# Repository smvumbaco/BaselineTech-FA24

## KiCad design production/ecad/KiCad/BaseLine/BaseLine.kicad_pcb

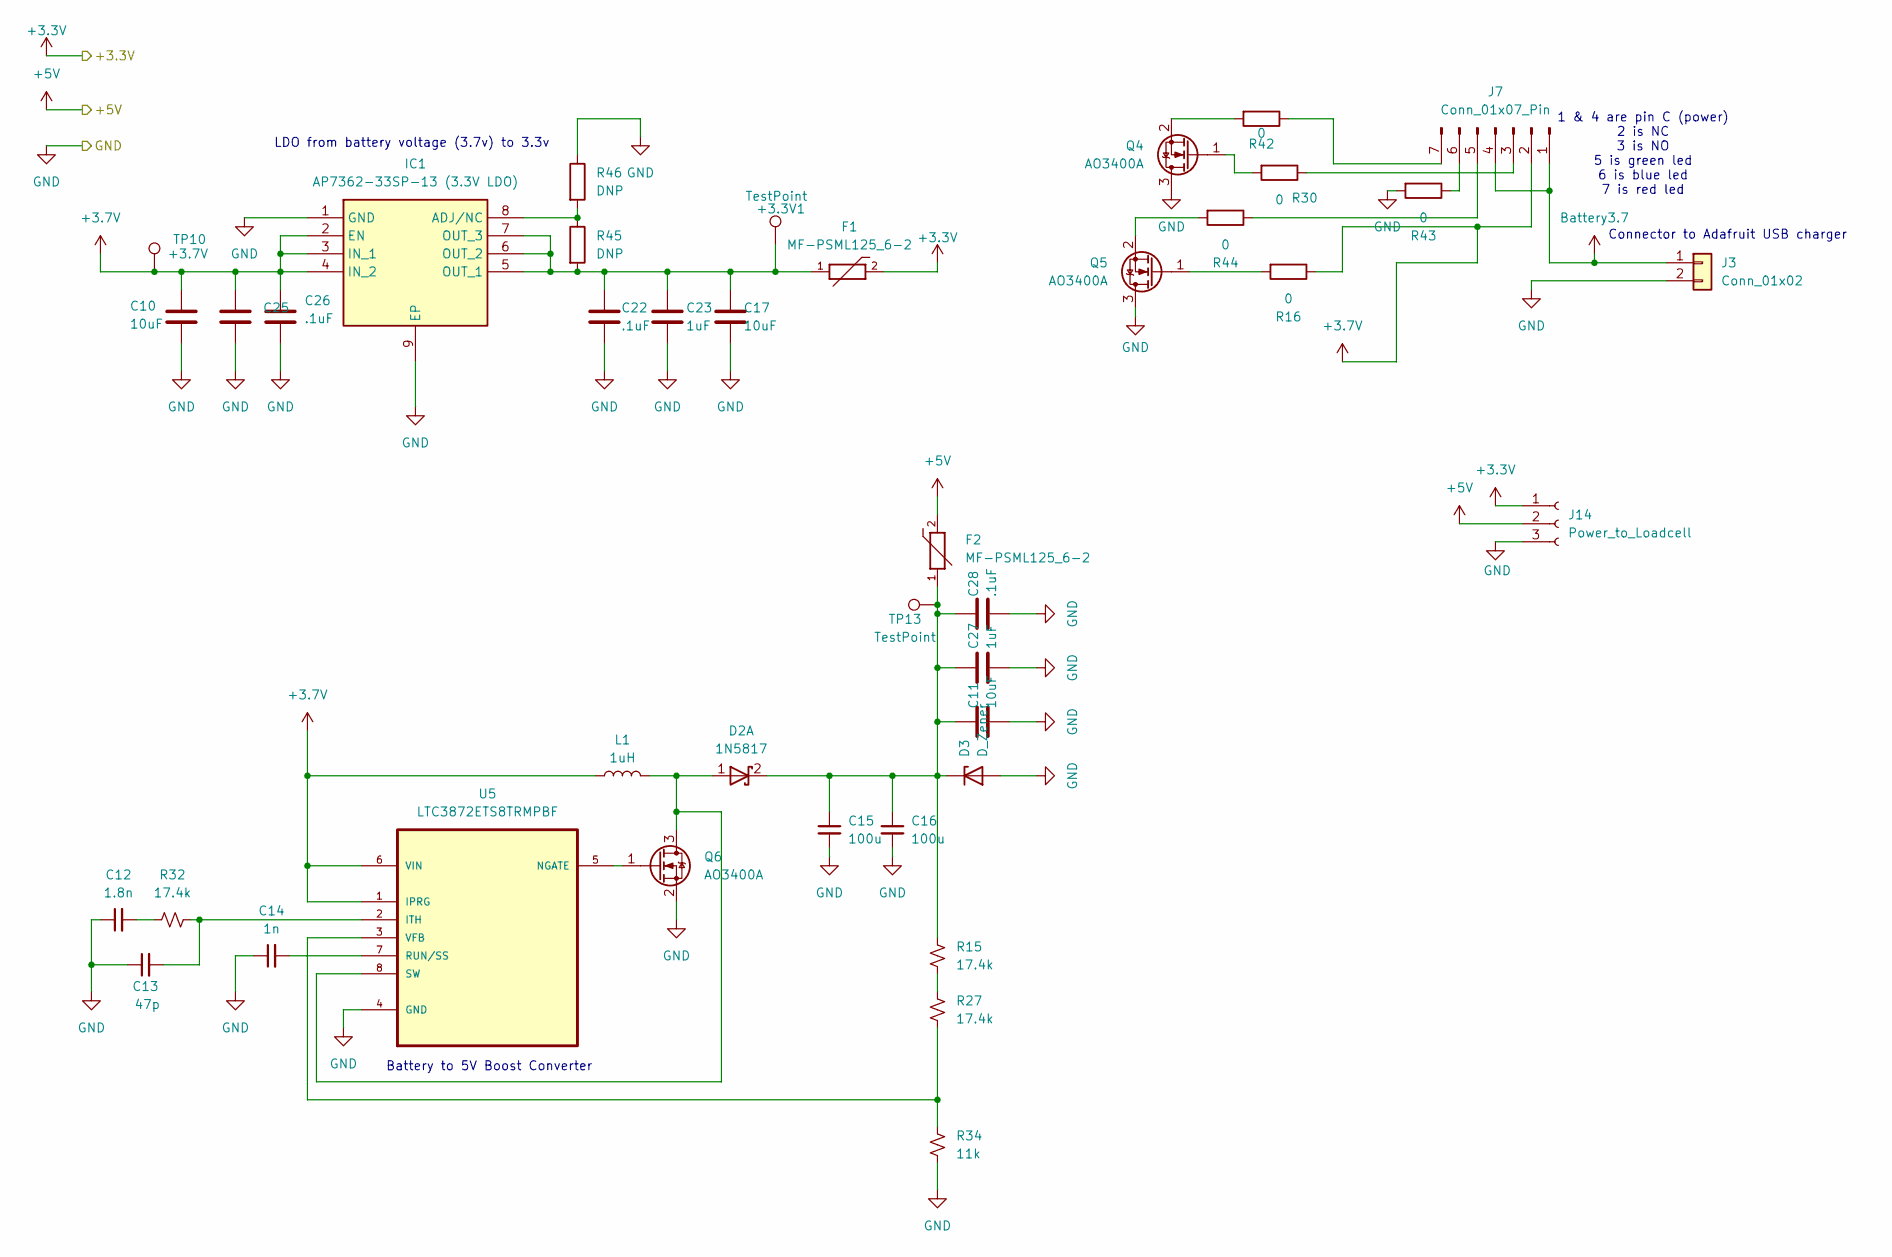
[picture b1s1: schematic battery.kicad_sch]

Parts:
+3.3V1: TestPoint; TestPoint_Pad_D1.5mm
C10, C11, C17: 10uF; C_0805_2012Metric
C12: 1.8n; C_0805_2012Metric
C13: 47p; C_0805_2012Metric
C14: 1n; C_0805_2012Metric
C15, C16: 100u; C_0805_2012Metric
C22, C26, C28: .1uF; C_0805_2012Metric
C23, C25, C27: 1uF; C_0805_2012Metric
D2: 1N5817; DO-41_STM
D3: D_Zener; DIOAD1165W56L425D185
F1, F2: MF-PSML125_6-2; FUSE_MF-PSML125_6-2; PARTREV C
IC1: AP7362-33SP-13 (3.3V LDO); SOIC127P600X163-9N; Mouser Part Number 621-AP7362-33SP-13
J3: Conn_01x02; JST_PH_B2B-PH-K_1x02_P2.00mm_Vertical
J7: Conn_01x07_Pin; JST_PH_B7B-PH-K_1x07_P2.00mm_Vertical
J14: Power_to_Loadcell; JST_EH_B3B-EH-A_1x03_P2.50mm_Vertical
L1: 1uH; L_0805_2012Metric_Pad1.05x1.20mm_HandSolder
Q4, Q5, Q6: AO3400A; SOT-23
R15, R27, R32: 17.4k; R_0805_2012Metric
R16, R30, R42, R43, R44: 0; R_0805_2012Metric
R34: 11k; R_0805_2012Metric
R45, R46: DNP; R_0805_2012Metric
TP10: +3.7V; TestPoint_Pad_2.0x2.0mm
TP13: TestPoint; TestPoint_Pad_2.0x2.0mm
U5: LTC3872ETS8TRMPBF; SOT65P280X100-8N; MPN LTC3872ETS8#TRMPBF

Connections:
+3.3V: F1.2, J14.1; also elsewhere on the board
+3.7V: C10.2, C25.2, C26.2, IC1.2 (EN), IC1.3 (IN_1), IC1.4 (IN_2), J7.2, L1.1, R16.1, TP10.1, U5.1 (IPRG), U5.6 (VIN)
+5V: F2.2, J14.2; also elsewhere on the board
Battery3.7: J3.1, J7.1, J7.4
GND: C10.1, C11.1, C12.1, C13.1, C14.1, C15.2, C16.2, C17.1, C22.1, C23.1, C25.1, C26.1, C27.1, C28.1, D3.2 (A), IC1.1 (GND), IC1.9 (EP), J3.2, J14.3, Q4.3 (D), Q5.3 (D), Q6.2 (S), R34.2, R43.2, R46.1, U5.4 (GND); also elsewhere on the board
unnamed: C12.2, R32.1
unnamed: D2.1 (A), L1.2, Q6.3 (D), U5.8 (SW)
unnamed: C11.2, C15.1, C16.1, C27.2, C28.2, D2.2 (K), D3.1 (K), F2.1, R15.2, TP13.1
unnamed: IC1.8 (ADJ/NC), R45.1, R46.2
unnamed: +3.3V1.1, C17.2, C22.2, C23.2, F1.1, IC1.5 (OUT_1), IC1.6 (OUT_2), IC1.7 (OUT_3), R45.2
unnamed: J7.3, R30.1
unnamed: J7.5, R44.1
unnamed: J7.6, R43.1
unnamed: J7.7, R42.1
unnamed: Q4.1 (G), R30.2
unnamed: Q4.2 (S), R42.2
unnamed: Q5.1 (G), R16.2
unnamed: Q5.2 (S), R44.2
unnamed: Q6.1 (G), U5.5 (NGATE)
unnamed: R15.1, R27.2
unnamed: C13.2, R32.2, U5.2 (ITH)
unnamed: C14.2, U5.7 (RUN/SS)
unnamed: R27.1, R34.1, U5.3 (VFB)

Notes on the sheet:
1 & 4 are pin C (power) 2 is NC 3 is NO 5 is green led 6 is blue led 7 is red led
LDO from battery voltage (3.7v) to 3.3v
Battery to 5V Boost Converter
Connector to Adafruit USB charger

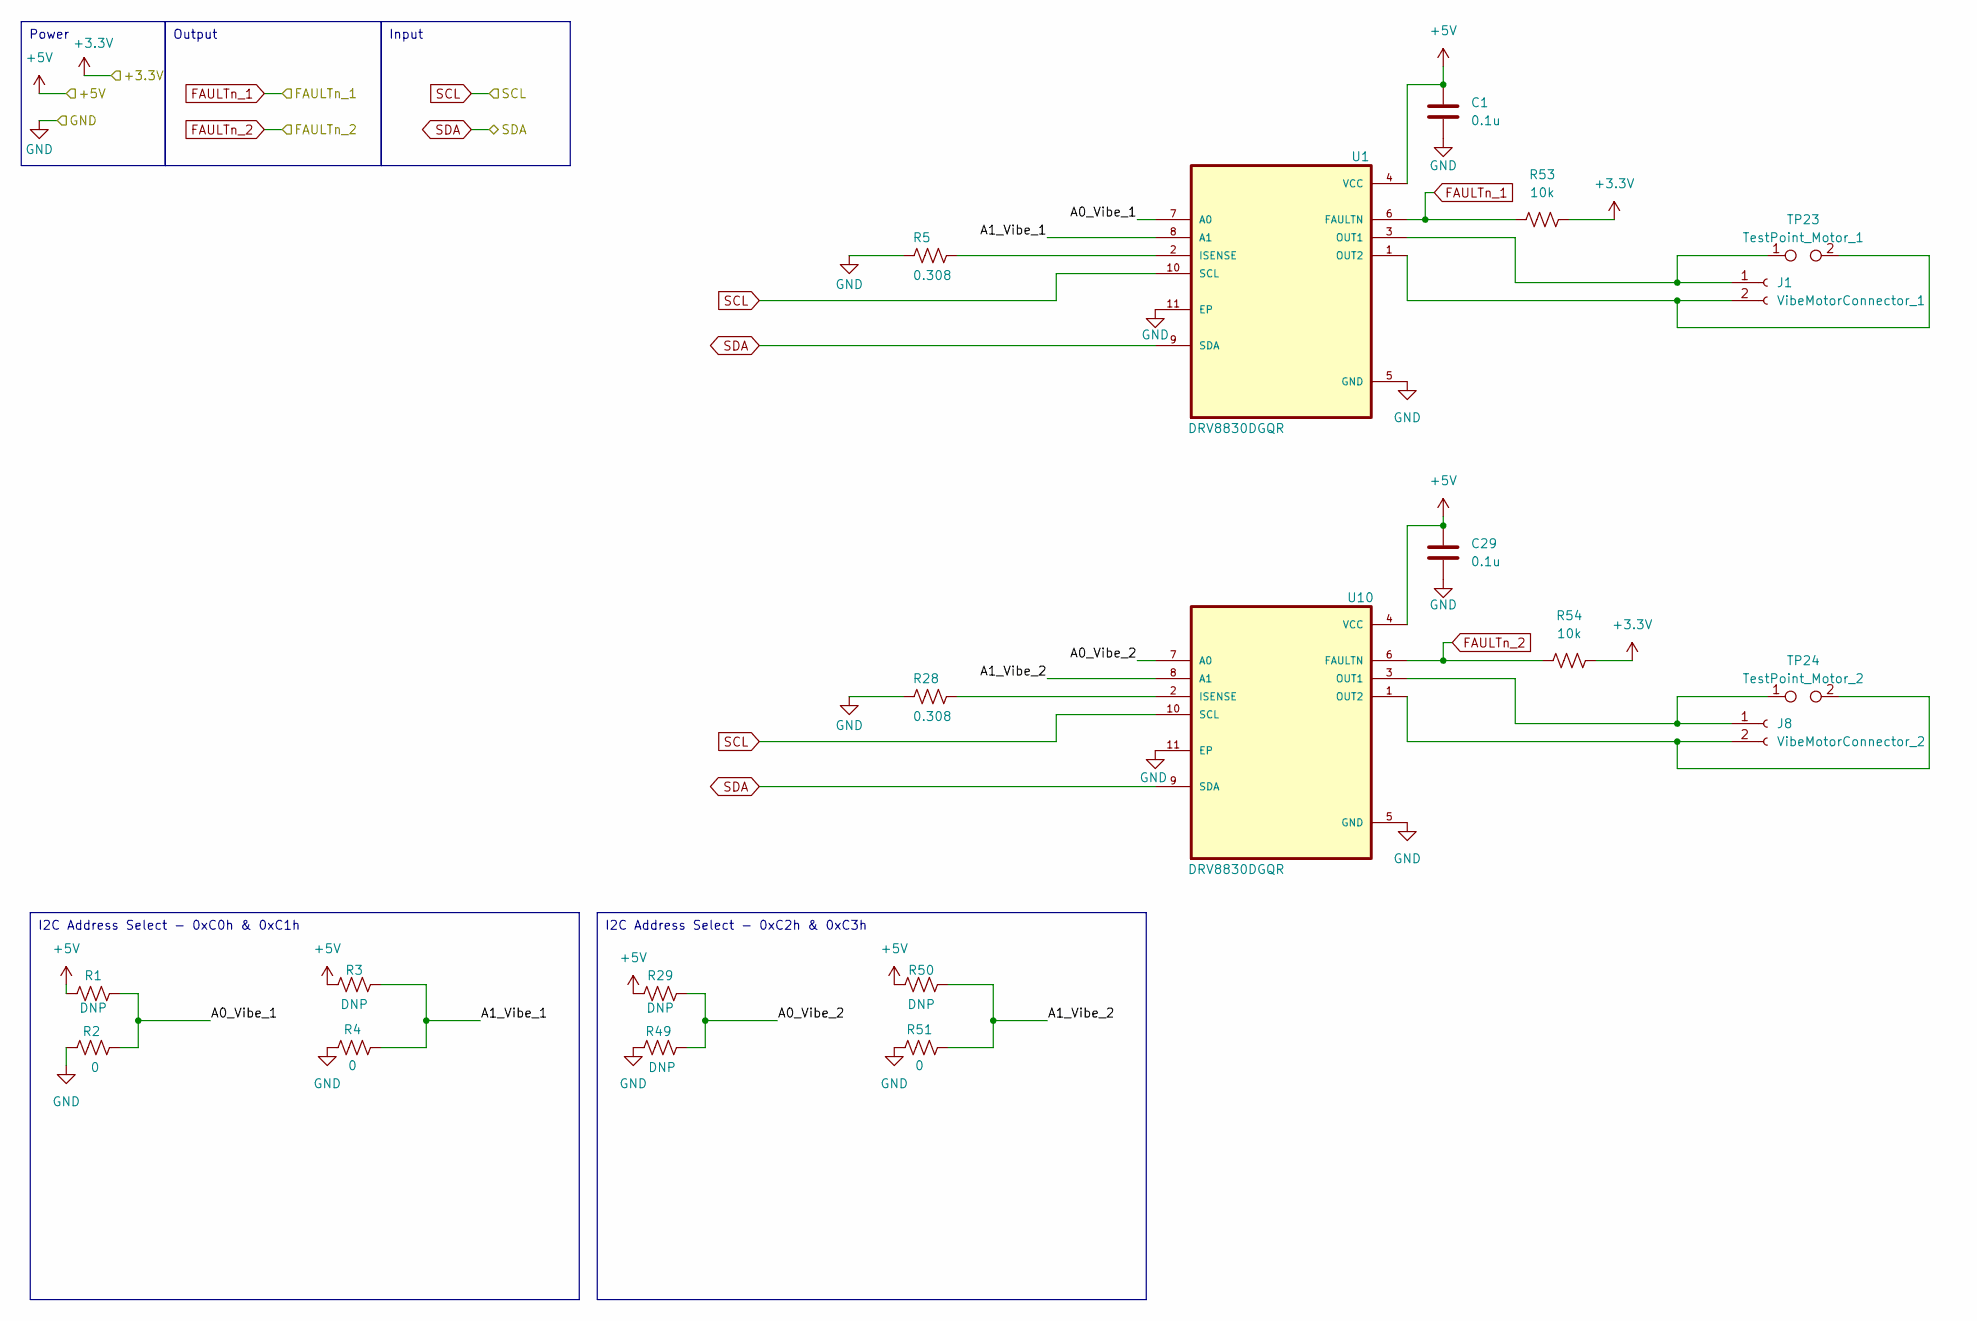
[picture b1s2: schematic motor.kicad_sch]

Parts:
C1, C29: 0.1u; C_0805_2012Metric_Pad1.18x1.45mm_HandSolder
J1: VibeMotorConnector_1; JST_B2B-XH-A
J8: VibeMotorConnector_2; JST_B2B-XH-A
R1, R3, R29, R49, R50: DNP; R_0805_2012Metric_Pad1.20x1.40mm_HandSolder
R2, R4, R51: 0; R_0805_2012Metric_Pad1.20x1.40mm_HandSolder
R5, R28: 0.308; R_0805_2012Metric_Pad1.20x1.40mm_HandSolder
R53, R54: 10k; R_0805_2012Metric_Pad1.20x1.40mm_HandSolder
TP23: TestPoint_Motor_1; TestPoint_2Pads_Pitch2.54mm_Drill0.8mm
TP24: TestPoint_Motor_2; TestPoint_2Pads_Pitch2.54mm_Drill0.8mm
U1, U10: DRV8830DGQR; IC_XTR111AIDGQR

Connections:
+3.3V: R53.2, R54.2; also elsewhere on the board
+5V: C1.1, C29.1, R1.1, R3.1, R29.1, R50.1, U1.4 (VCC), U10.4 (VCC); also elsewhere on the board
/Motor/A0_Vibe_1: R1.2, R2.2, U1.7 (A0)
/Motor/A0_Vibe_2: R29.2, R49.2, U10.7 (A0)
/Motor/A1_Vibe_1: R3.2, R4.2, U1.8 (A1)
/Motor/A1_Vibe_2: R50.2, R51.2, U10.8 (A1)
FAULTn_1: R53.1, U1.6 (FAULTN); also elsewhere on the board
FAULTn_2: R54.1, U10.6 (FAULTN); also elsewhere on the board
GND: C1.2, C29.2, R2.1, R4.1, R5.2, R28.2, R49.1, R51.1, U1.5 (GND), U1.11 (EP), U10.5 (GND), U10.11 (EP); also elsewhere on the board
unnamed: J1.1, TP23.1, U1.3 (OUT1)
unnamed: J1.2, TP23.2, U1.1 (OUT2)
unnamed: J8.1, TP24.1, U10.3 (OUT1)
unnamed: J8.2, TP24.2, U10.1 (OUT2)
unnamed: R5.1, U1.2 (ISENSE)
unnamed: R28.1, U10.2 (ISENSE)
SCL: U1.10 (SCL), U10.10 (SCL); also elsewhere on the board
SDA: U1.9 (SDA), U10.9 (SDA); also elsewhere on the board

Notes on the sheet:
Power
I2C Address Select - 0xC0h & 0xC1h
I2C Address Select - 0xC2h & 0xC3h
Output
Input

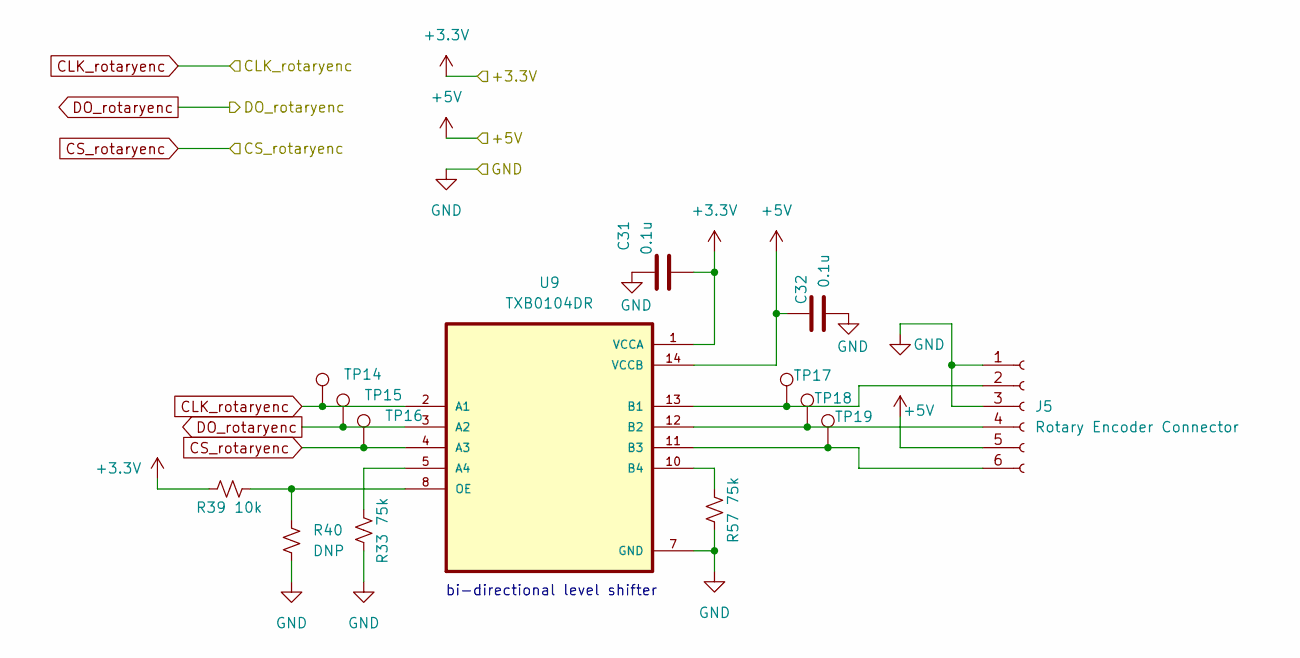
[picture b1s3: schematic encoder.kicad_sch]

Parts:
C31, C32: 0.1u; C_0805_2012Metric_Pad1.18x1.45mm_HandSolder
J5: Rotary Encoder Connector; JST_EH_B6B-EH-A_1x06_P2.50mm_Vertical
R33, R57: 75k; R_0805_2012Metric_Pad1.20x1.40mm_HandSolder
R39: 10k; R_0805_2012Metric_Pad1.20x1.40mm_HandSolder
R40: DNP; R_0805_2012Metric_Pad1.20x1.40mm_HandSolder
TP14, TP15, TP16, TP17, TP18, TP19: TestPoint_Pad_2.0x2.0mm
U9: TXB0104DR; SOIC127P600X175-14N

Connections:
+3.3V: C31.2, R39.1, U9.1 (VCCA); also elsewhere on the board
+5V: C32.1, J5.5, U9.14 (VCCB); also elsewhere on the board
CLK_rotaryenc: TP14.1, U9.2 (A1); also elsewhere on the board
CS_rotaryenc: TP16.1, U9.4 (A3); also elsewhere on the board
DO_rotaryenc: TP15.1, U9.3 (A2); also elsewhere on the board
GND: C31.1, C32.2, J5.1, J5.3, R33.1, R40.2, R57.1, U9.7 (GND); also elsewhere on the board
unnamed: J5.2, TP17.1, U9.13 (B1)
unnamed: J5.4, TP18.1, U9.12 (B2)
unnamed: J5.6, TP19.1, U9.11 (B3)
unnamed: R33.2, U9.5 (A4)
unnamed: R57.2, U9.10 (B4)
unnamed: R39.2, R40.1, U9.8 (OE)

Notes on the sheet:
bi-directional level shifter

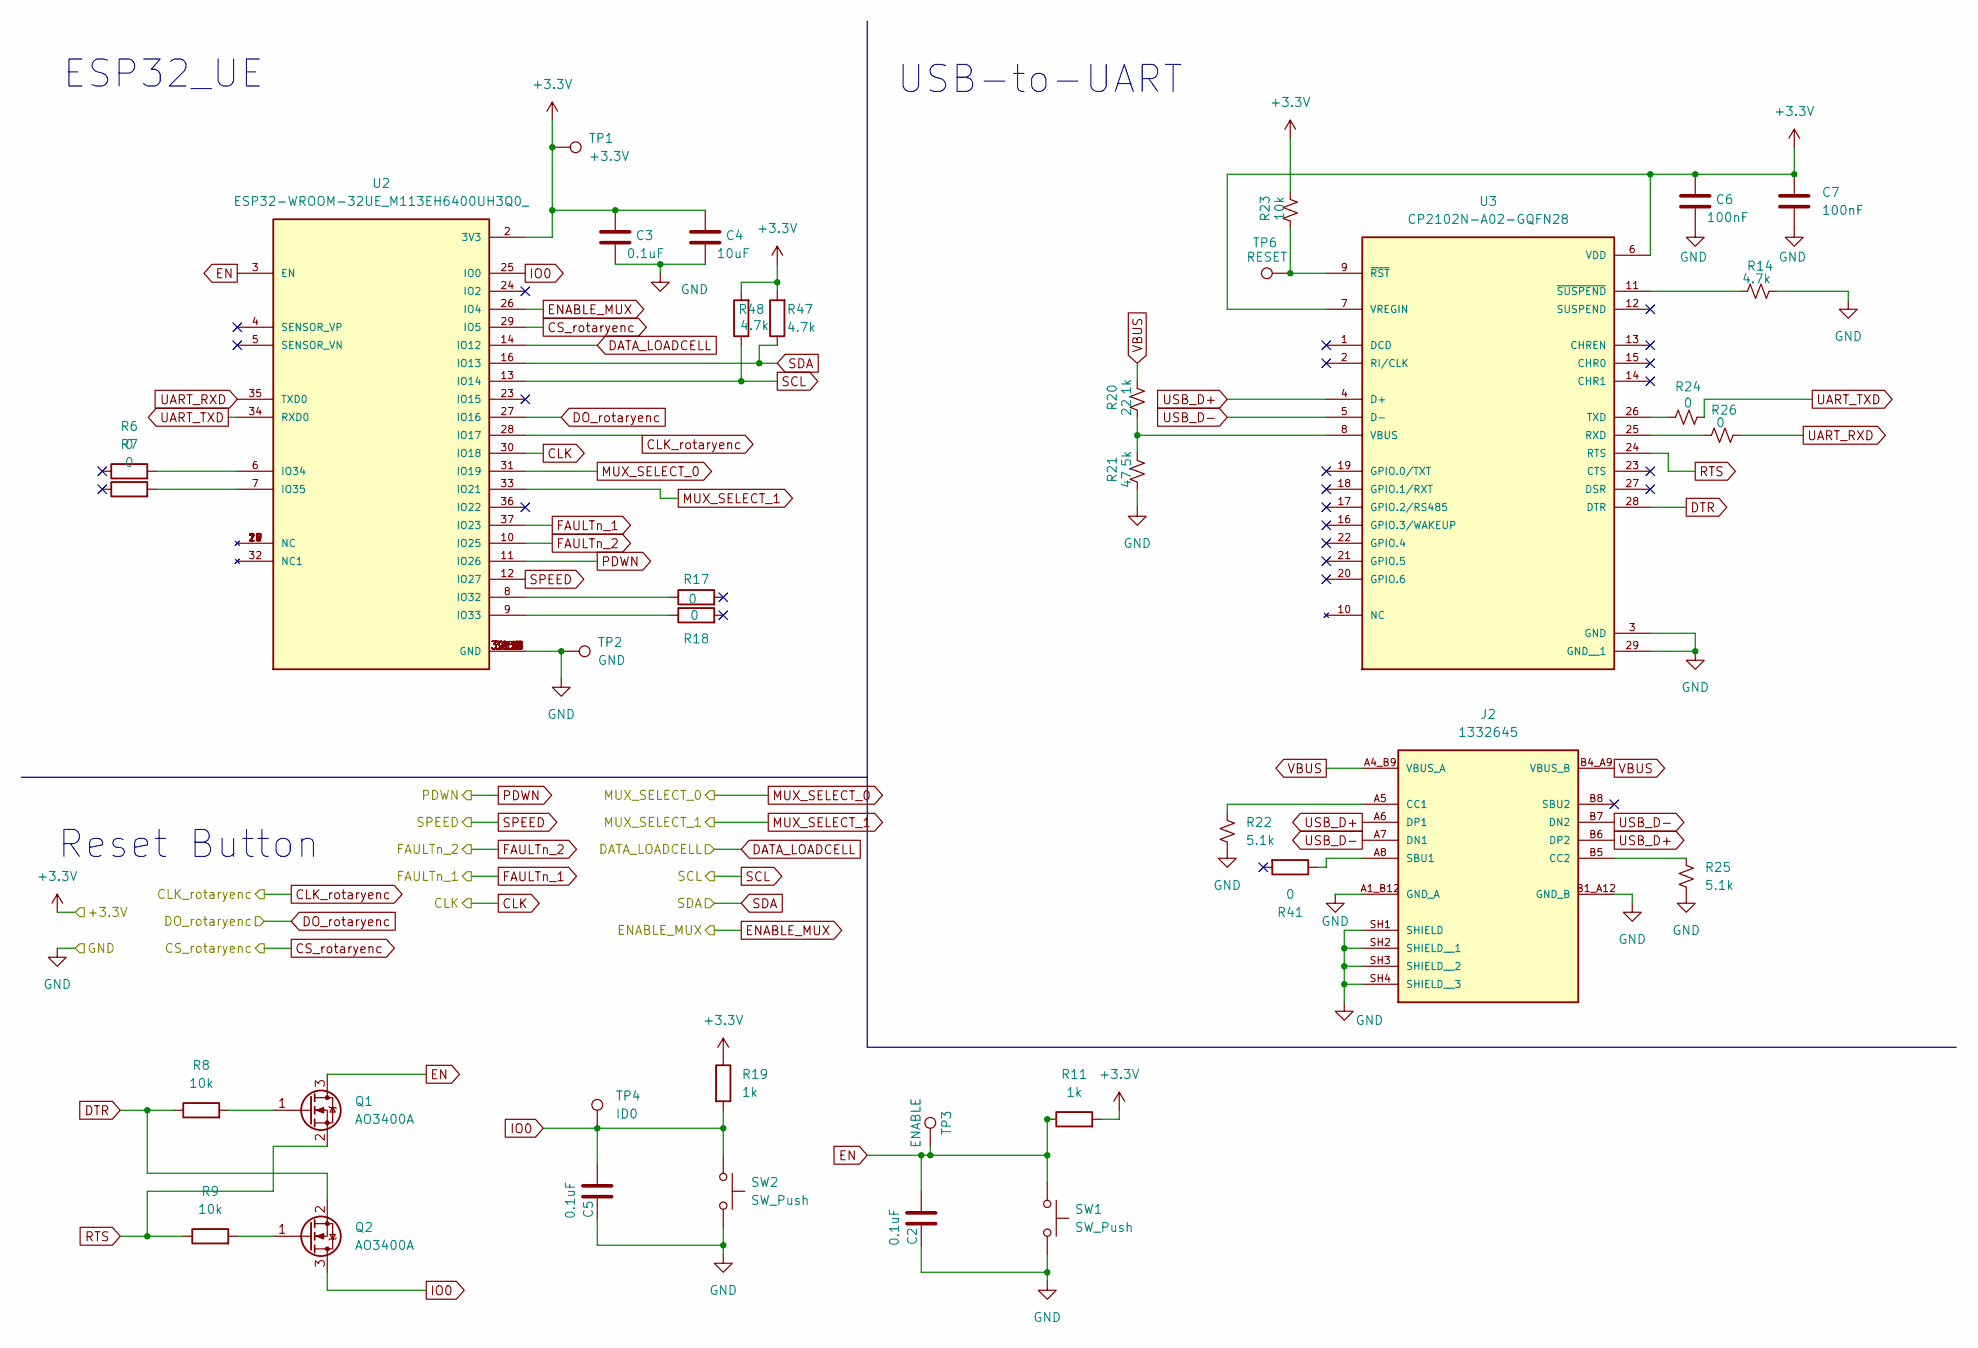
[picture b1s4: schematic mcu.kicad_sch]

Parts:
C2, C3, C5: 0.1uF; C_0805_2012Metric
C4: 10uF; C_0805_2012Metric
C6, C7: 100nF; C_0805_2012Metric
J2: 1332645; PHOENIX_1332645; PARTREV 17.01.2022
Q1, Q2: AO3400A; SOT-23
R6, R7, R17, R18, R24, R26, R41: 0; R_0805_2012Metric
R8, R9, R23: 10k; R_0805_2012Metric
R11, R19: 1k; R_0805_2012Metric
R14, R47, R48: 4.7k; R_0805_2012Metric
R20: 22.1k; R_0805_2012Metric
R21: 47.5k; R_0805_2012Metric
R22: 5.1k; R_0805_2012Metric_Pad1.20x1.40mm_HandSolder
R25: 5.1k; R_0805_2012Metric
SW1, SW2: SW_Push; SW_1825910-6-4
TP1: +3.3V; TestPoint_Pad_2.0x2.0mm
TP2: GND; TestPoint_Pad_2.0x2.0mm
TP3: ENABLE; TestPoint_Pad_2.0x2.0mm
TP4: ID0; TestPoint_Pad_2.0x2.0mm
TP6: RESET; TestPoint_Pad_2.0x2.0mm
U2: ESP32-WROOM-32UE_M113EH6400UH3Q0_; MODULE_ESP32-WROOM-32UE_M113EH6400UH3Q0_; PARTREV 1.2
U3: CP2102N-A02-GQFN28; QFN50P500X500X80-29N; PARTREV 1.5

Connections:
+3.3V: C3.1, C4.1, C6.1, C7.1, R11.2, R19.1, R23.1, R47.2, R48.2, TP1.1, U2.2 (3V3), U3.6 (VDD), U3.7 (VREGIN); also elsewhere on the board
CLK: U2.30 (IO18); also elsewhere on the board
CLK_rotaryenc: U2.28 (IO17); also elsewhere on the board
CS_rotaryenc: U2.29 (IO5); also elsewhere on the board
DATA_LOADCELL: U2.14 (IO12); also elsewhere on the board
DO_rotaryenc: U2.27 (IO16); also elsewhere on the board
DTR: Q2.2 (S), R8.1, U3.28 (DTR)
EN: C2.1, Q1.3 (D), R11.1, SW1.1, TP3.1, U2.3 (EN)
ENABLE_MUX: U2.26 (IO4); also elsewhere on the board
FAULTn_1: U2.37 (IO23); also elsewhere on the board
FAULTn_2: U2.10 (IO25); also elsewhere on the board
GND: C2.2, C3.2, C4.2, C5.2, C6.2, C7.2, J2.A1_B12 (GND_A), J2.B1_A12 (GND_B), J2.SH1 (SHIELD), J2.SH2 (SHIELD__1), J2.SH3 (SHIELD__2), J2.SH4 (SHIELD__3), R14.1, R21.2, R22.2, R25.2, SW1.2, SW2.2, TP2.1, U2.1 (GND), U2.15 (GND), U2.38 (GND), U2.39_1 (GND), U2.39_2 (GND), U2.39_3 (GND), U2.39_4 (GND), U2.39_5 (GND), U2.39_6 (GND), U2.39_7 (GND), U2.39_8 (GND), U2.39_9 (GND), U2.39_10 (GND), U2.39_11 (GND), U2.39_12 (GND), U2.39_13 (GND), U2.39_14 (GND), U2.39_15 (GND), U2.39_16 (GND), U2.39_17 (GND), U2.39_18 (GND), U2.39_19 (GND), U2.39_20 (GND), U2.39_21 (GND), U3.3 (GND), U3.29 (GND__1); also elsewhere on the board
IO0: C5.1, Q2.3 (D), R19.2, SW2.1, TP4.1, U2.25 (IO0)
MUX_SELECT_0: U2.31 (IO19); also elsewhere on the board
MUX_SELECT_1: U2.33 (IO21); also elsewhere on the board
unnamed: J2.A5 (CC1), R22.1
unnamed: J2.B5 (CC2), R25.1
unnamed: J2.A8 (SBU1), R41.1
unnamed: Q1.1 (G), R8.2
unnamed: Q2.1 (G), R9.2
unnamed: R17.1, U2.8 (IO32)
unnamed: R18.1, U2.9 (IO33)
unnamed: R6.2, U2.6 (IO34)
unnamed: R7.2, U2.7 (IO35)
unnamed: R26.2, U3.25 (RXD)
unnamed: R24.2, U3.26 (TXD)
unnamed: R20.2, R21.1, U3.8 (VBUS)
unnamed: R23.2, TP6.1, U3.9 (~RST)
unnamed: R14.2, U3.11 (~SUSPEND)
PDWN: U2.11 (IO26); also elsewhere on the board
RTS: Q1.2 (S), R9.1, U3.24 (RTS)
SCL: R48.1, U2.13 (IO14); also elsewhere on the board
SDA: R47.1, U2.16 (IO13); also elsewhere on the board
SPEED: U2.12 (IO27); also elsewhere on the board
UART_RXD: R26.1, U2.35 (TXD0)
UART_TXD: R24.1, U2.34 (RXD0)
USB_D+: J2.A6 (DP1), J2.B6 (DP2), U3.4 (D+)
USB_D-: J2.A7 (DN1), J2.B7 (DN2), U3.5 (D-)
VBUS: J2.A4_B9 (VBUS_A), J2.B4_A9 (VBUS_B), R20.1

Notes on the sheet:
Reset Button
USB-to-UART
ESP32_UE

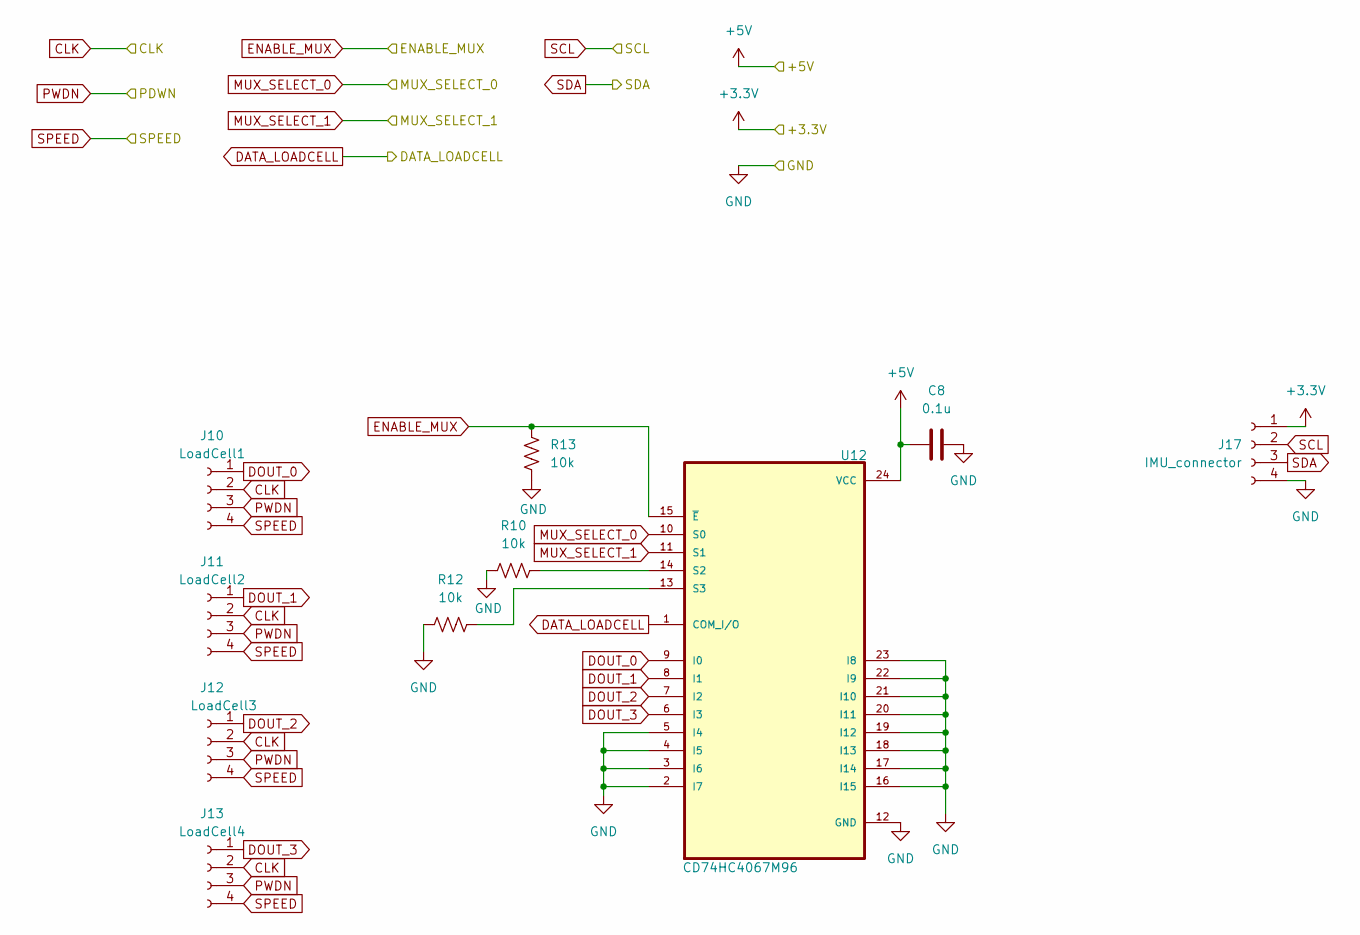
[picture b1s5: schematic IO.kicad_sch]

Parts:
C8: 0.1u; C_0805_2012Metric_Pad1.18x1.45mm_HandSolder
J10: LoadCell1; CONN_B4B-XH-AM_JST
J11: LoadCell2; CONN_B4B-XH-AM_JST
J12: LoadCell3; CONN_B4B-XH-AM_JST
J13: LoadCell4; CONN_B4B-XH-AM_JST
J17: IMU_connector; CONN_B4B-XH-AM_JST
R10, R12, R13: 10k; R_0805_2012Metric_Pad1.20x1.40mm_HandSolder
U12: CD74HC4067M96; SOIC127P1030X265-24N

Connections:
+3.3V: J17.1; also elsewhere on the board
+5V: C8.1, U12.24 (VCC); also elsewhere on the board
CLK: J10.2, J11.2, J12.2, J13.2; also elsewhere on the board
DATA_LOADCELL: U12.1 (COM_I/O); also elsewhere on the board
DOUT_0: J10.1, U12.9 (I0)
DOUT_1: J11.1, U12.8 (I1)
DOUT_2: J12.1, U12.7 (I2)
DOUT_3: J13.1, U12.6 (I3)
ENABLE_MUX: R13.2, U12.15 (~E); also elsewhere on the board
GND: C8.2, J17.4, R10.1, R12.1, R13.1, U12.2 (I7), U12.3 (I6), U12.4 (I5), U12.5 (I4), U12.12 (GND), U12.16 (I15), U12.17 (I14), U12.18 (I13), U12.19 (I12), U12.20 (I11), U12.21 (I10), U12.22 (I9), U12.23 (I8); also elsewhere on the board
MUX_SELECT_0: U12.10 (S0); also elsewhere on the board
MUX_SELECT_1: U12.11 (S1); also elsewhere on the board
unnamed: R10.2, U12.14 (S2)
unnamed: R12.2, U12.13 (S3)
PDWN: J10.3, J11.3, J12.3, J13.3; also elsewhere on the board
SCL: J17.2; also elsewhere on the board
SDA: J17.3; also elsewhere on the board
SPEED: J10.4, J11.4, J12.4, J13.4; also elsewhere on the board

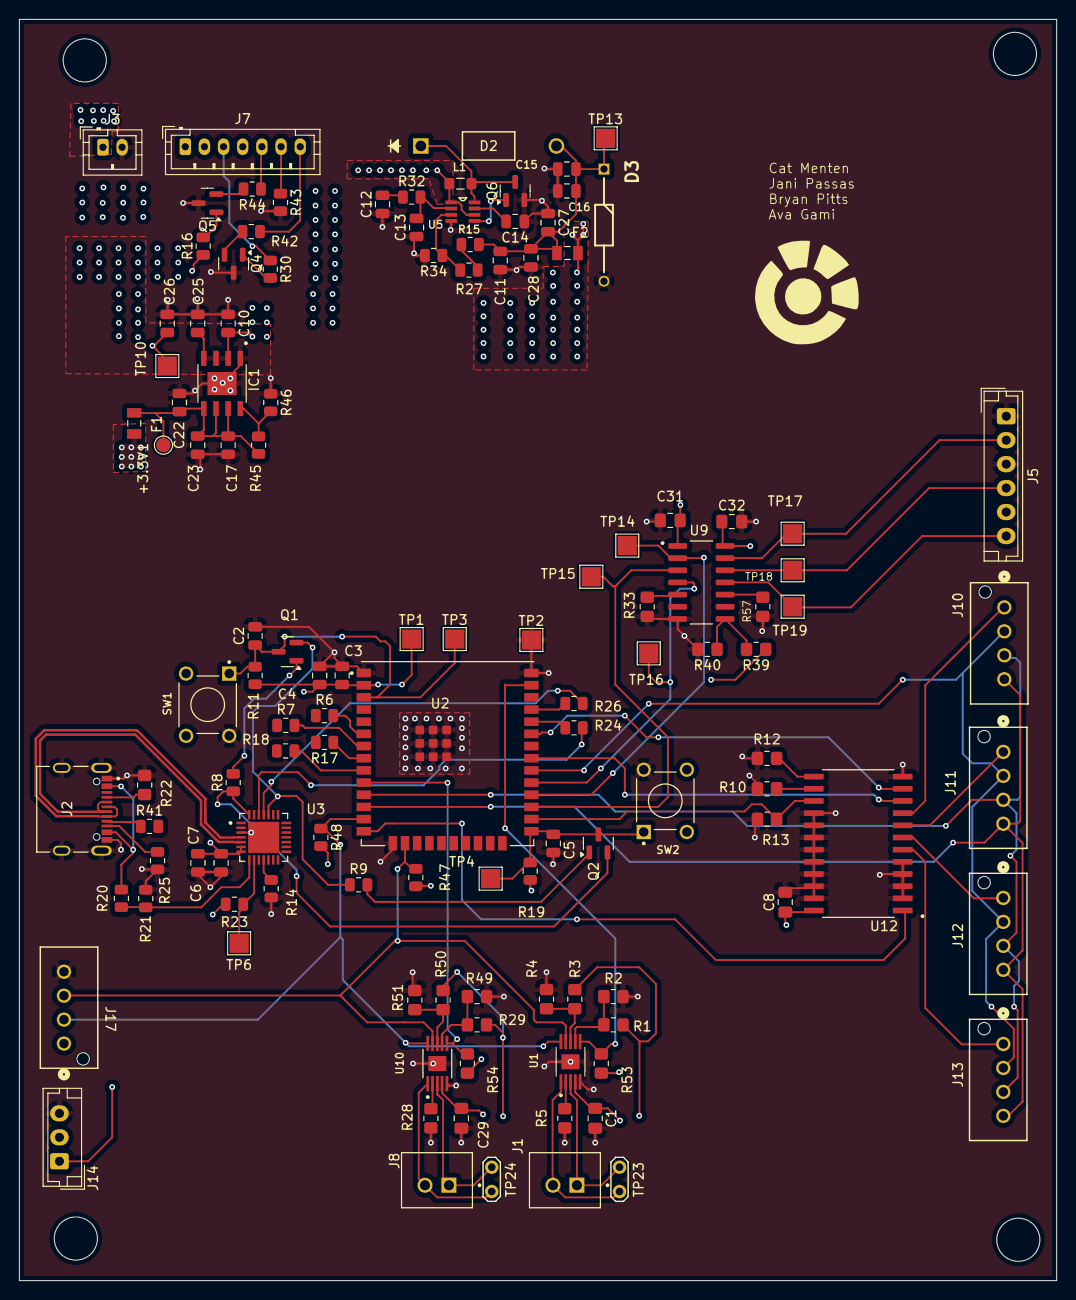
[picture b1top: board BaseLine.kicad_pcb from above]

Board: 4 copper layers, 108.2 x 131.6 mm, 122 parts (0 on the bottom side), 82 nets.

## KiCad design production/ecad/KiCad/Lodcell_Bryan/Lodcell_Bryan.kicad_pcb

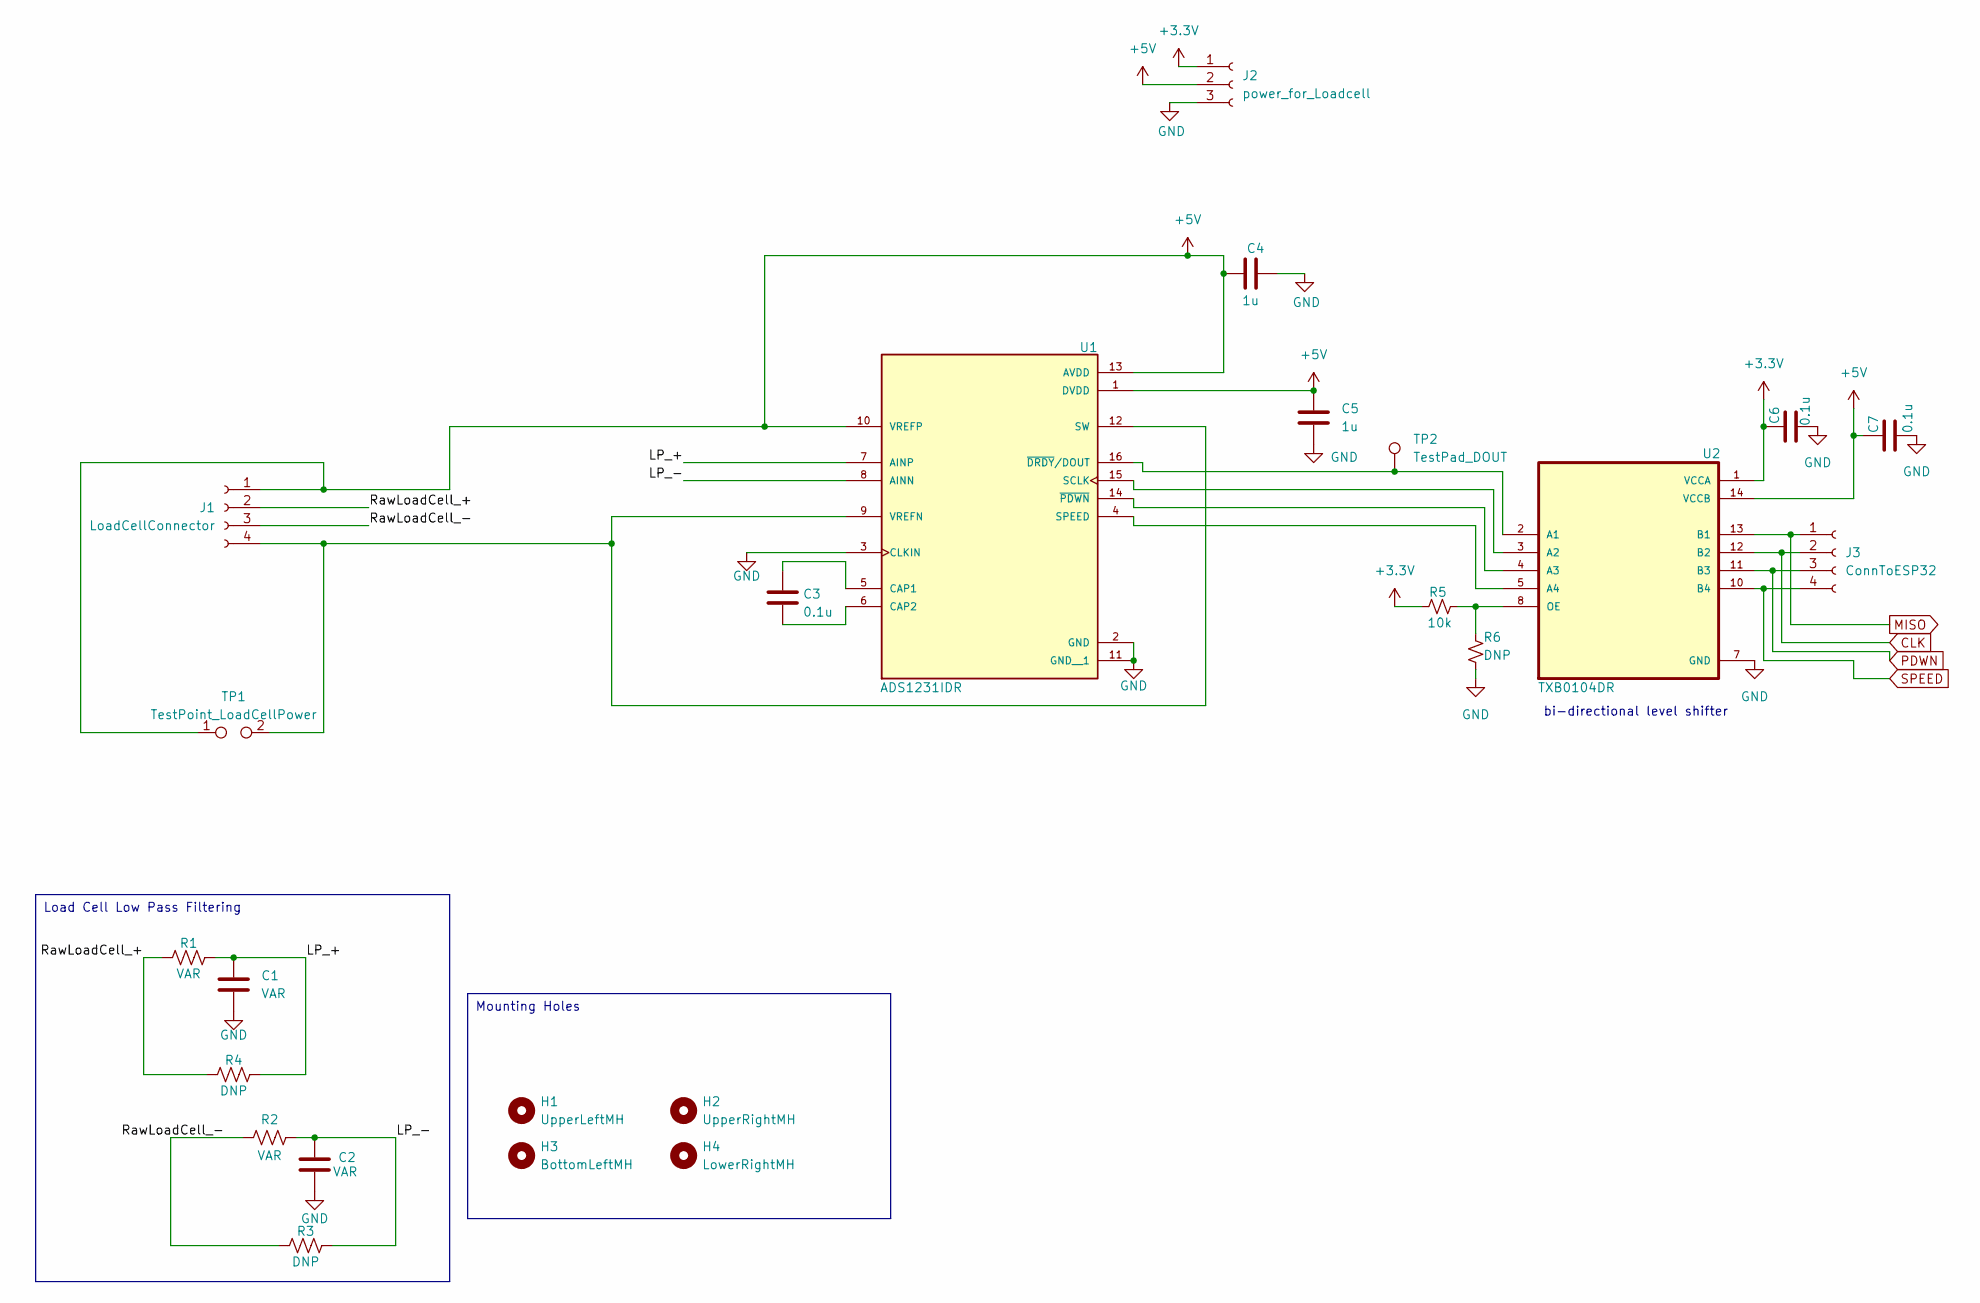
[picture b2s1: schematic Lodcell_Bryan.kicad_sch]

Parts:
C1, C2: VAR; C_0805_2012Metric_Pad1.18x1.45mm_HandSolder
C3, C6, C7: 0.1u; C_0805_2012Metric_Pad1.18x1.45mm_HandSolder
C4, C5: 1u; C_0805_2012Metric_Pad1.18x1.45mm_HandSolder
H1: UpperLeftMH; MountingHole_4.5mm
H2: UpperRightMH; MountingHole_4.5mm
H3: BottomLeftMH; MountingHole_4.5mm
H4: LowerRightMH; MountingHole_4.5mm
J1: LoadCellConnector; CONN_B4B-XH-AM_JST
J2: power_for_Loadcell; JST_EH_B3B-EH-A_1x03_P2.50mm_Vertical
J3: ConnToESP32; CONN_B4B-XH-AM_JST
R1, R2: VAR; R_0805_2012Metric_Pad1.20x1.40mm_HandSolder
R3, R4, R6: DNP; R_0805_2012Metric_Pad1.20x1.40mm_HandSolder
R5: 10k; R_0805_2012Metric_Pad1.20x1.40mm_HandSolder
TP1: TestPoint_LoadCellPower; TestPoint_2Pads_Pitch2.54mm_Drill0.8mm
TP2: TestPad_DOUT; TestPoint_Pad_D1.5mm
U1: ADS1231IDR; SOIC127P600X175-16N; PARTREV D
U2: TXB0104DR; SOIC127P600X175-14N

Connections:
+3.3V: C6.2, J2.1, R5.1, U2.1 (VCCA)
+5V: C4.1, C5.1, C7.2, J1.1, J2.2, TP1.1, U1.1 (DVDD), U1.10 (VREFP), U1.13 (AVDD), U2.14 (VCCB)
/LP_+: C1.1, R1.1, R4.1, U1.7 (AINP)
/LP_-: C2.2, R2.1, R3.1, U1.8 (AINN)
/RawLoadCell_+: J1.2, R1.2, R4.2
/RawLoadCell_-: J1.3, R2.2, R3.2
CLK: J3.2, U2.12 (B2)
GND: C1.2, C2.1, C4.2, C5.2, C6.1, C7.1, J2.3, R6.2, U1.2 (GND), U1.3 (CLKIN), U1.11 (GND__1), U2.7 (GND)
MISO: J3.1, U2.13 (B1)
unnamed: J1.4, TP1.2, U1.9 (VREFN), U1.12 (SW)
unnamed: C3.1, U1.5 (CAP1)
unnamed: C3.2, U1.6 (CAP2)
unnamed: U1.15 (SCLK), U2.3 (A2)
unnamed: U1.4 (SPEED), U2.5 (A4)
unnamed: TP2.1, U1.16 (~DRDY/DOUT), U2.2 (A1)
unnamed: U1.14 (~PDWN), U2.4 (A3)
unnamed: R5.2, R6.1, U2.8 (OE)
PDWN: J3.3, U2.11 (B3)
SPEED: J3.4, U2.10 (B4)

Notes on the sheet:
Mounting Holes
Load Cell Low Pass Filtering
bi-directional level shifter

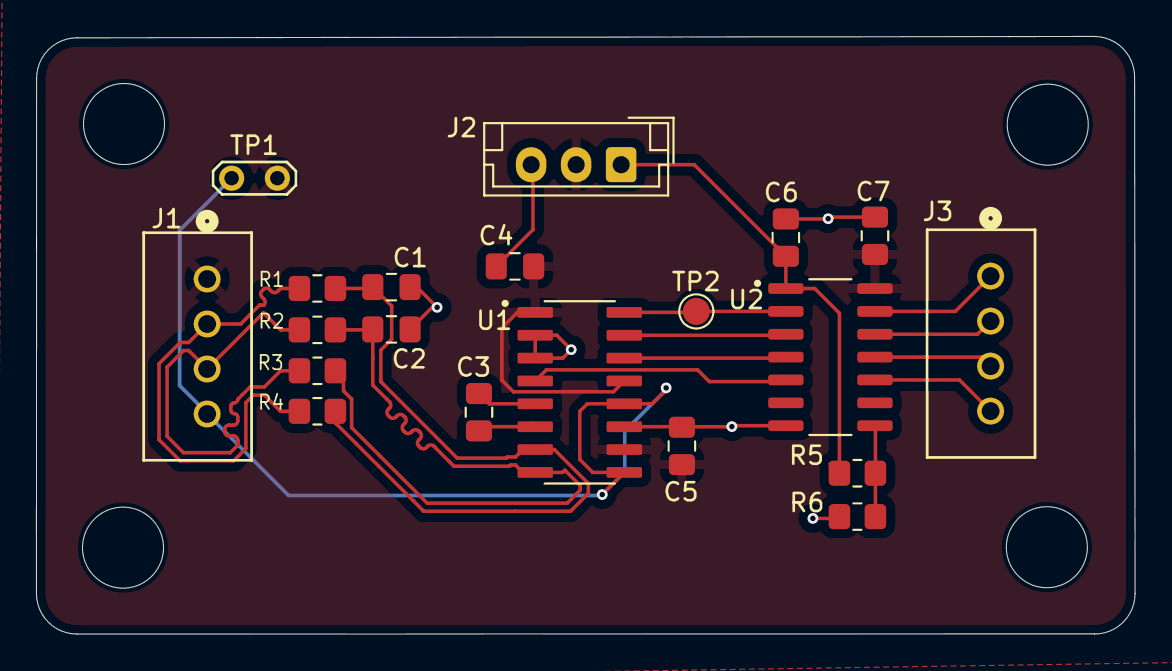
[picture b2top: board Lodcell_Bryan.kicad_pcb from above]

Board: 2 copper layers, 61.0 x 33.2 mm, 24 parts (0 on the bottom side), 19 nets.

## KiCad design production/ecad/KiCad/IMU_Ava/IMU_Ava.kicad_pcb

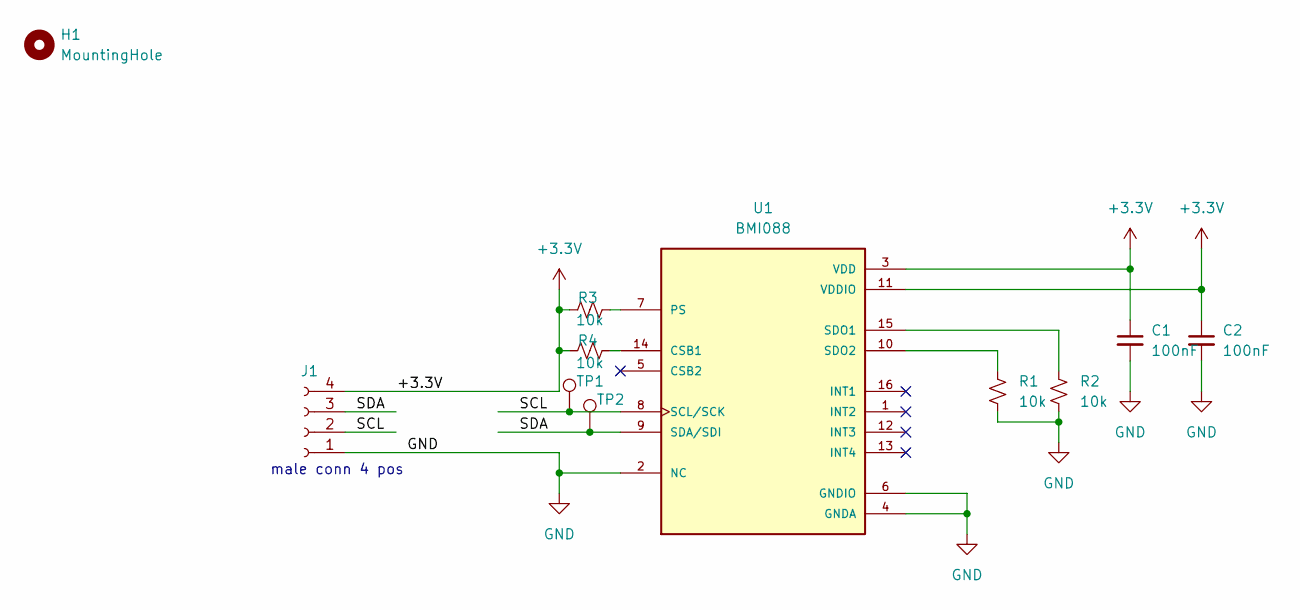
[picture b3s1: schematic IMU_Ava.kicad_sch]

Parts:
C1, C2: 100nF; C_0805_2012Metric_Pad1.18x1.45mm_HandSolder
H1: MountingHole
J1: Conn_01x04_Socket; JST_EH_S4B-EH_1x04_P2.50mm_Horizontal
R1, R2, R3, R4: 10k; R_0805_2012Metric_Pad1.20x1.40mm_HandSolder
TP1, TP2: TestPoint_Pad_D1.5mm
U1: BMI088; PQFN50P450X300X100-16N

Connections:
+3.3V: C1.1, C2.1, J1.4, R3.1, R4.1, U1.3 (VDD), U1.11 (VDDIO)
/SCL: J1.2, TP1.1, U1.8 (SCL/SCK)
/SDA: J1.3, TP2.1, U1.9 (SDA/SDI)
GND: C1.2, C2.2, J1.1, R1.2, R2.2, U1.2 (NC), U1.4 (GNDA), U1.6 (GNDIO)
unnamed: R4.2, U1.14 (CSB1)
unnamed: R3.2, U1.7 (PS)
unnamed: R2.1, U1.15 (SDO1)
unnamed: R1.1, U1.10 (SDO2)

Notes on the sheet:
male conn 4 pos

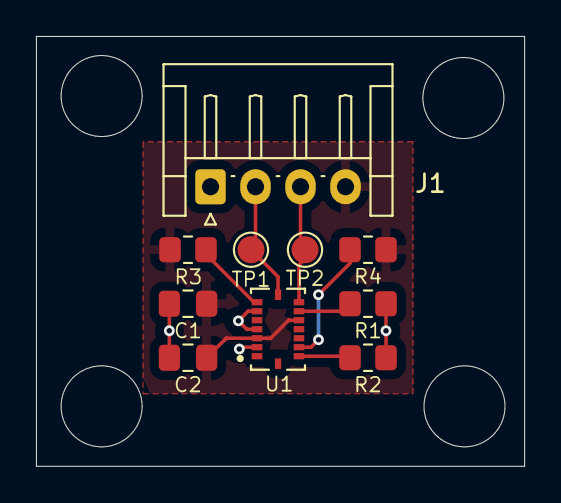
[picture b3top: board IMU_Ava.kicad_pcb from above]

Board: 2 copper layers, 27.1 x 23.9 mm, 10 parts (0 on the bottom side), 8 nets.
